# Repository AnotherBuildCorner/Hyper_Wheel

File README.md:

# Multi-Layer Embedded HID Interface with Rotary Input

A programmable HID control interface that replaces discrete key presses with continuous rotary input, enabling precise, context-aware interaction for workflows like video editing and CAD.

**Codename:** Hyper_Wheel

## Engineering Summary

- 4-layer mixed-signal embedded system (98 × 65 mm) based on nRF52840 (BLE + USB HID)
- RF-aware PCB layout with calculated 50Ω antenna trace on TG155 FR4
- Battery-powered architecture (LiPo + charger + protection + load switching)
- Multi-bus I²C system separating OLED displays and encoders for signal integrity
- Designed within JLCPCB DFM constraints (no blind vias, optimized BOM, 0402/0603 preference)
- Staged bring-up strategy using XIAO validation platform to decouple firmware and hardware risk

> > 4-layer mixed-signal PCB with dense MCU fanout, controlled routing, and separated power/RF domains
---

## What This Demonstrates

This project demonstrates the ability to:

- Design a mixed-signal embedded system with RF considerations  
- Make system-level tradeoffs under real constraints (power, layout, manufacturability)  
- Identify and mitigate risk without full simulation tooling  
- Structure hardware bring-up and validation intentionally  

This is not a proof-of-concept—it is a system designed to be built, debugged, and iterated.

---

## Status

- Rev A PCB complete and ready for fabrication  
- Validation hardware in production  
- Firmware development in progress  

---

## Intended Outcome

The goal of this project is to produce a fully functional, portable HID control surface that can be:

- Built using standard PCB manufacturing workflows  
- Assembled and validated without specialized RF tooling  
- Used in real workflows without custom drivers or software dependencies  

Success is defined by reliable operation, predictable behavior, and ease of integration into existing systems.

---

## Concept

### Early Concept Render

> *Early prototype render shown for system concept demonstration. Mechanical design is still evolving.*

Hyper Wheel is a rotary-first HID control surface designed to replace discrete macro inputs with continuous, context-aware control.

The system combines:
- High-resolution rotary encoder input  
- Programmable key matrix  
- Onboard display feedback  

Primary use cases:
- Video editing (timeline scrubbing, precision control)  
- CAD navigation  
- General HID-based workflows  

The design prioritizes:
- Compact form factor  
- Driverless operation (USB/BLE HID only)  
- Integration of continuous and discrete input into a single interface  
---

## System Overview

Hyper Wheel is a programmable HID macro device built around a high-resolution magnetic encoder, designed to provide precise, context-aware control.

Unlike typical macro pads:
- Primary input is continuous (rotary), not discrete  
- Output is standard HID (keyboard + mouse)  
- Feedback is integrated via dual OLED displays  

The system is designed for enterprise compatibility:
- No custom drivers  
- USB and BLE HID only  

Current development focuses on validating:
- Power architecture  
- Multi-layer PCB layout with RF considerations  
- Scalable I/O architecture  

## System Architecture

```mermaid
flowchart LR

%% Power Path
USB[USB 5V] --> CHG[LiPo Charger]
BAT[LiPo Battery] --> PROT[Protection Circuit]
PROT --> CHG
CHG --> SYS[nRF52840 VDDH + Internal Regulator]
PROT --> VMON[ADC Batt Divider]
VMON --> MCU_ADC

%% Core System
SYS --> NRF[nRF52840 MCU] 
SYS --> LS[Load Switches]

%% Peripheral Power
LS --> OLED[Dual OLED Displays]
LS --> ENC[AS5600 Encoders]

%% Data / Control
NRF --> I2C1[I2C Bus 1]
NRF <--> I2C2[I2C Bus 2]
NRF --> LS
I2C1 --> OLED
I2C2 <--> ENC

%% Inputs
KEYS[Keyswitches on GPIO] --> NRF

%% Host Communication
NRF <--> USBDATA[USB 2.0]
NRF --> BLE[BLE]
USBDATA <--> HOST[Host Computer]
BLE --> HOST
```

## Key Features

- nRF52840-based system with **BLE + USB HID support**  
- High-resolution **magnetic encoder (AS5600-based)**  
- Dual **I2C OLED displays** for contextual UI feedback  
- **User-defined key mapping** (firmware-controlled)  
- **Left/right-hand agnostic layout** with mode switching  
- **LiPo + USB power architecture**  
- Modular sensor and expansion strategy  
- Fully **driverless operation (standard HID only)**  

---

## Engineering Highlights

### Single-MCU USB + BLE Architecture
- Transitioned from QFN48 to USB-capable aQFN73 to enable USB HID while maintaining BLE
- Preserved single-MCU architecture to reduce system complexity

### Battery-First Power System
- Implemented Nordic VDDH Config 4 architecture for battery-first operation
- USB used for detection only; system powered from charger output
- Enabled internal DC/DC (DCDCEN0/1), eliminating need for external regulator

### RF Design Approach
- Used reference antenna layout with controlled ground zones
- Calculated 50Ω impedance trace for 2.4 GHz operation on TG155 FR4
- Designed for short-range BLE use (desktop device)
- Validation deferred to hardware bring-up

### Routing Density & Layer Strategy
- Moved key matrix to inner layer to reduce congestion
- Improved fanout of high-density MCU region
- Optimized via sizing for manufacturing cost

### Iteration Strategy (Firmware First)
- Developed XIAO-based validation board to decouple firmware and hardware bring-up
- Allows testing of UI, input pipeline, and HID behavior before full PCB assembly

### Constraint-Driven Design

- Designed without access to RF simulation or SI toolchains, relying on first-principles reasoning and reference layouts to achieve first-pass success  
- Applied calculated trace geometry and conservative design margins to mitigate signal integrity risk  
- Prioritized manufacturability and iteration speed over theoretical optimization  
- Structured design to enable validation through hardware bring-up rather than pre-simulation

---

## Key Engineering Decisions

- **Single-MCU architecture (nRF52840)**  
  Reduced system complexity while supporting both BLE and USB HID

- **Battery-first power design (VDDH Config 4)**  
  Enabled seamless USB + battery operation without conflicting domains

- **Split I²C buses**  
  Prevented address conflicts and improved signal integrity under expansion

- **HID-only communication (no custom drivers)**  
  Ensures enterprise compatibility and plug-and-play behavior

- **Staged bring-up using validation hardware**  
  Reduced risk by separating firmware development from full system assembly

- **Conservative RF design without simulation tooling**  
  Relied on reference layouts and controlled geometry with validation deferred to hardware
---

## Validation Status

| Area | Status |
|------|--------|
| Power System | Not yet characterized under load |
| RF Performance | Not validated (no RF test equipment available) |
| USB Signal Integrity | Not measured |
| I2C Stability | Not stress-tested |
| Firmware Integration | In progress |

> Validation strategy is structured to isolate failure modes early, reducing system-level debugging complexity during full integration

> Firmware bring-up and subsystem testing occurring prior to full hardware integration.

---

## Power Profile (Preliminary)

The following figures are early design estimates based on component datasheets and expected operating modes. Final values will be validated during bring-up.

### Component-Level Current Estimates

| Component / Mode | Estimated Current | Notes |
|------|------:|------|
| nRF52840, BLE active (+8 dBm) | 14.8 mA | Active BLE operating point on 3.3 V rail |
| OLED display (each) | 12–20 mA | 0.96" Winstar OLED at 3.3 V, ~50% illumination |
| AS5600 encoder (each, active) | 6.4 mA | Active measurement mode |
| Keyswitches | ~0 mA | No static consumption |
| nRF52840 system-off, RAM retained, wake on GPIOTE | 2.36 µA | MCU-only low-power state |

### Estimated System Current

| System Mode | Estimated Current | Notes |
|------|------:|------|
| Active, one OLED + one encoder + BLE | ~33.2–41.2 mA | 14.8 + 12–20 + 6.4 |
| Active, two OLEDs + one encoder + BLE | ~45.2–61.2 mA | Current main-board target configuration |
| Active, two OLEDs + two encoders + BLE | ~51.6–67.6 mA | Higher-end fully populated case |
| Deep sleep / system-off | ~33 µA | Includes MCU, charger, protection IC, hall sensor, FET leakage, and battery divider |

### Estimated Runtime (2000 mAh LiPo)

| Mode | Estimated Runtime |
|------|------:|
| 45.2 mA active draw | ~44 hours |
| 61.2 mA active draw | ~33 hours |
| 67.6 mA active draw | ~30 hours |
| 33 µA sleep current | ~6.9 years theoretical |

Sleep-current validation will also include key-matrix wake behavior, since retained GPIO pullups can dominate standby current if not configured carefully.

> Sleep-mode runtime is a first-order electrical estimate only and does not account for battery self-discharge, cell aging, converter losses, or environmental effects.

> These values are estimates and will be validated during hardware bring-up.

##  Hardware Overview

The following images highlight key aspects of the PCB design, including routing strategy, RF layout considerations, and multi-layer power distribution.

---

### Full PCB Layout (Routing View)

> Overall PCB layout showing multi-layer routing strategy, peripheral distribution, and controlled RF region placement.

---

##  MCU / RF Region Detail

### Top Layer (Routing)

> nRF52840 fanout and high-density routing region, including USB interface routing and transition into a controlled antenna region.

---

### Ground Reference Layer

> Ground reference layer showing return path continuity, stitching strategy, and antenna clearance region.

---

### Power Distribution Layer || Metal 4

> Multi-zone power distribution separating 3.3V, Load domains, and ground to reduce coupling and improve system stability.

---

##  Layer Stack & Power Distribution

### Full Ground Plane || Metal 3

> Continuous ground plane providing low-impedance return paths across the board and supporting RF performance.

---

### Full Signal Plane || Metal 2

> Second layer signal plane for BGA fanout.

---

### Full Top Plane || Metal 1

> Primary signal plane with all zone ground.

---

##  Dev Platform / Prototype

> Simplified firmware validation platform based on the XIAO nRF52840, enabling rapid iteration of firmware and UI behavior prior to full hardware validation.

### Dev System Architecture

```mermaid
flowchart LR

%% Power Path
USB[USB 5V] --> CHG[XIAO Onboard LiPo Charger]
BAT[LiPo Battery] --> PROT[Protection Circuit]
PROT --> CHG
CHG --> SYS[XIAO VDDH + Internal Regulator]
PROT --> VMON[ADC Batt Divider]
VMON --> MCU_ADC

%% Core System
SYS --> NRF[nRF52840 MCU] 

%% Peripheral Power
SYS --> OLED[Dual OLED Displays]
SYS --> ENC[AS5600 Encoders]

%% Data / Control
NRF <--> I2C1[I2C Bus 1]
I2C1 <--> OLED
I2C1 <--> ENC

%% Inputs
KEYS[Keyswitches on GPIO] --> NRF

%% Host Communication
NRF <--> USBDATA[USB 2.0]
NRF --> BLE[BLE]
USBDATA <--> HOST[Host Computer]
BLE --> HOST
```

---

## Hardware Iterations

### Rev A – Firmware Validation Platform
- XIAO nRF52840-based
- Reduced feature set to validate input, display, and HID stack
- 2-layer board for reduced cost/complexity

.png>) 
> Rev A Board.

.png>)
> Rev B board, note change in keyswitch footprints and added jumper network
### Rev B – Connector + Layout Refinement
- Introduced JST right-angle connectors (2/4/6 pin)
- Retained 2.54mm headers for bring-up flexibility
- Implemented rotationally symmetric connector layout
  - Enables cross-compatibility between 4-pin and 6-pin harnesses
  - Increased routing complexity but improved wiring consistency
- Adjusted OLED power routing for improved modularity

.png>).png>)
> Right shows the reconfigurable jumper array to switch GND and VCC pins to OLED

### Key Takeaways
- Connector standardization impacts both layout complexity and user error rate
- Bring-up flexibility is worth temporary redundancy (2.54 + JST)
- Physical interface decisions cascade into firmware, assembly, and usability

## Design for Manufacturing (DFM)

This design explicitly considers **PCBA cost and manufacturability**, not just functionality.

- Designed within standard JLCPCB capabilities (no blind vias, no via-in-pad)  
- Optimized via sizing for cost  
- Minimized use of 0201 components where not required  
- Favoring 0402 / 0603 for improved assembly yield  
- Reducing unique BOM values (ongoing)

This ensures the design is **practical for real-world assembly**, not just theoretical performance.

---

##  Assembly / 3D Model

.png>)
> Not all components have linked 3D models. USB and Keyswitches not shown
---

## Current Status

### Hardware
- Main PCB: Ready for fabrication (Rev A)  
- XIAO-based validation boards: Fabricated, awaiting delivery  
- Power architecture implemented (VDDH-based system)  
- Multi-layer routing and RF region defined  
- Test points and debug access integrated  

### Firmware
- Early development in progress (PlatformIO)  
- HID architecture defined (USB + BLE)  
- Encoder and display integration in progress  
- UI/UX layer not yet implemented  

### Mechanical
- Concept prototype complete (wheel + macro pad)  
- Final enclosure design pending  
- Mounting and integration strategy in development  

---

### Next Milestones

1. Bring-up XIAO validation platform  
2. Validate encoder and OLED pipeline  
3. Verify power behavior under real load  
4. Assemble Rev A main board  
5. Begin enclosure integration  

---

## Design Constraints

- Designed for standard PCB manufacturing (JLCPCB) with no blind/buried vias  
- Limited board size due to encoder geometry and enclosure constraints  
- Required HID-only communication for enterprise compatibility  
- Power system designed around single-cell LiPo with safe charge/discharge behavior

### Key Tradeoffs

- Chose single-MCU (nRF52840) over multi-chip architecture to reduce system complexity at the cost of tighter routing constraints  
- Accepted lack of RF simulation tooling and relied on reference layout + conservative design margins  
- Used internal VDDH regulation to simplify power architecture, trading off external regulator flexibility  
- Split I2C buses to manage address conflicts and maintain signal integrity under expansion

---
## Use Cases

**Primary**
- Video editing (timeline scrubbing, precision control)

**Secondary**
- CAD navigation  
- General productivity workflows  
- Custom macro environments  

---

## Future Work

### Firmware

- Development of configurable HID mapping system  
- Exploration of QMK/ZMK compatibility with encoder-based input  
- Potential on-device configuration interface via OLED UI  

### Mechanical

- Final enclosure design around encoder and key layout  
- Mounting strategy for PCB and battery integration  
- Ergonomic considerations for left/right-handed use

---

## Design Philosophy

- Use **standard HID** instead of custom drivers  
- Prioritize **iteration speed over theoretical perfection**  
- Design within **real manufacturing constraints**  
- Document decisions and tradeoffs explicitly

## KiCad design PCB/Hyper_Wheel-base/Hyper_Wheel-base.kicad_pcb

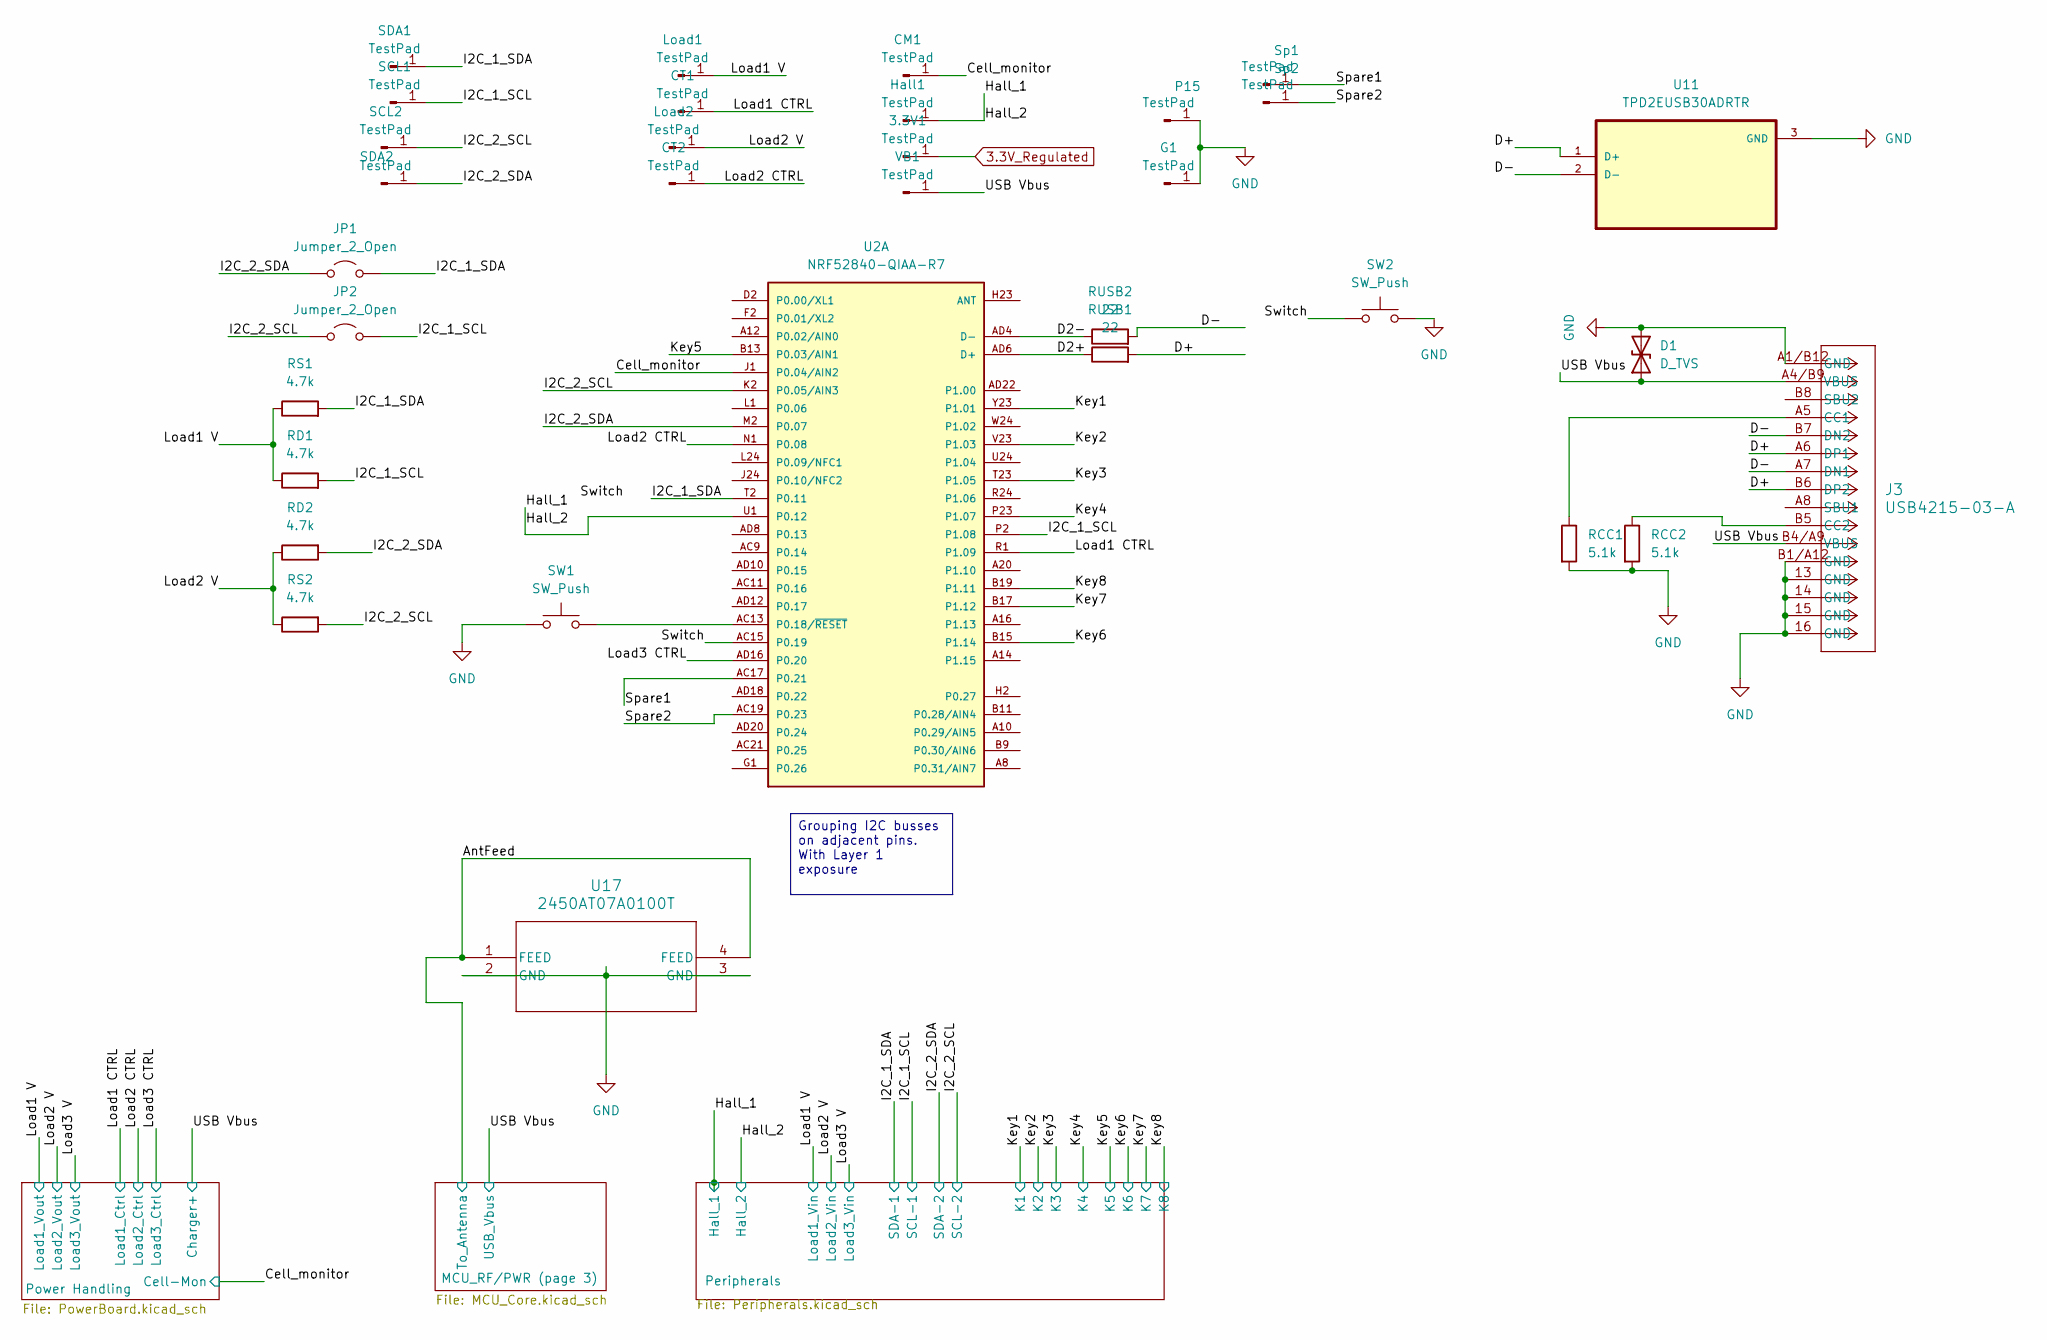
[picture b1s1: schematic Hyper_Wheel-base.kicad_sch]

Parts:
3.3V1: TestPad; TestPoint_Pad_D1.0mm
CM1: TestPad; TestPoint_Pad_D1.0mm
CT1, CT2: TestPad; TestPoint_Pad_D1.0mm
D1: D_TVS; D_0603_1608Metric
G1: TestPad; TestPoint_Pad_D1.0mm
Hall1: TestPad; TestPoint_Pad_D1.0mm
J3: USB4215-03-A; USBC-CONN_8p94X6p5X3p16_12L_GCC
JP1, JP2: Jumper_2_Open; SolderJumper-2_P1.3mm_Open_Pad1.0x1.5mm
Load1, Load2: TestPad; TestPoint_Pad_D1.0mm
P15: TestPad; TestPoint_Pad_D1.0mm
RCC1, RCC2: 5.1k; R_0402_1005Metric
RD1, RD2: 4.7k; R_0402_1005Metric
RS1, RS2: 4.7k; R_0402_1005Metric
RUSB1, RUSB2: 22; R_0402_1005Metric
SCL1, SCL2: TestPad; TestPoint_Pad_D1.0mm
SDA1, SDA2: TestPad; TestPoint_Pad_D1.0mm
SW1, SW2: SW_Push; SW_SPST_PTS647_Sx38
Sp1, Sp2: TestPad; TestPoint_Pad_D1.0mm
U2: NRF52840-QIAA-R7; NORDIC_NRF52840-QIAA-R7; PARTREV 1.2
U11: TPD2EUSB30ADRTR; SOT-323_SC-70
U17: 2450AT07A0100T; 2450AT07A0100T_JOT+Keepout
VB1: TestPad; TestPoint_Pad_D1.0mm

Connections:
3.3V_Regulated: 3.3V1.1 (Pin_1_1); also elsewhere on the board
/AntFeed: U17.1 (FEED), U17.4 (FEED); also elsewhere on the board
/Cell_monitor: CM1.1 (Pin_1_1), U2.J1 (P0.04/AIN2); also elsewhere on the board
/D2+: RUSB1.1, U2.AD6 (D+)
/D2-: RUSB2.1, U2.AD4 (D-)
/D+: J3.A6 (DP1), J3.B6 (DP2), RUSB1.2, U11.1 (D+)
/D-: J3.A7 (DN1), J3.B7 (DN2), RUSB2.2, U11.2 (D-)
/Hall_1: Hall1.1 (Pin_1_1), U2.U1 (P0.12); also elsewhere on the board
/I2C_1_SCL: JP2.2 (B), RD1.2, SCL1.1 (Pin_1_1), U2.P2 (P1.08); also elsewhere on the board
/I2C_1_SDA: JP1.2 (B), RS1.2, SDA1.1 (Pin_1_1), U2.T2 (P0.11); also elsewhere on the board
/I2C_2_SCL: JP2.1 (A), RS2.2, SCL2.1 (Pin_1_1), U2.K2 (P0.05/AIN3); also elsewhere on the board
/I2C_2_SDA: JP1.1 (A), RD2.2, SDA2.1 (Pin_1_1), U2.M2 (P0.07); also elsewhere on the board
/Key1: U2.Y23 (P1.01); also elsewhere on the board
/Key2: U2.V23 (P1.03); also elsewhere on the board
/Key3: U2.T23 (P1.05); also elsewhere on the board
/Key4: U2.P23 (P1.07); also elsewhere on the board
/Key5: U2.B13 (P0.03/AIN1); also elsewhere on the board
/Key6: U2.B15 (P1.14); also elsewhere on the board
/Key7: U2.B17 (P1.12); also elsewhere on the board
/Key8: U2.B19 (P1.11); also elsewhere on the board
/Load1 CTRL: CT1.1 (Pin_1_1), U2.R1 (P1.09); also elsewhere on the board
/Load1 V: Load1.1 (Pin_1_1), RD1.1, RS1.1; also elsewhere on the board
/Load2 CTRL: CT2.1 (Pin_1_1), U2.N1 (P0.08); also elsewhere on the board
/Load2 V: Load2.1 (Pin_1_1), RD2.1, RS2.1; also elsewhere on the board
/Load3 CTRL: U2.AD16 (P0.20)
/Spare1: Sp1.1 (Pin_1_1), U2.AC17 (P0.21)
/Spare2: Sp2.1 (Pin_1_1), U2.AC19 (P0.23)
/Switch: SW2.1, U2.AC15 (P0.19)
/USB Vbus: D1.1 (A1), J3.A4/B9 (VBUS), J3.B4/A9 (VBUS), VB1.1 (Pin_1_1); also elsewhere on the board
GND: D1.2 (A2), G1.1 (Pin_1_1), J3.13 (GND), J3.14 (GND), J3.15 (GND), J3.16 (GND), J3.A1/B12 (GND), J3.B1/A12 (GND), P15.1 (Pin_1_1), RCC1.2, RCC2.2, SW1.1, SW2.2, U11.3 (GND), U17.2 (GND), U17.3 (GND); also elsewhere on the board
unnamed: J3.A5 (CC1), RCC1.1
unnamed: J3.B5 (CC2), RCC2.1
unnamed: SW1.2, U2.AC13 (P0.18/~RESET)
unnamed 57: U2.H23 (ANT); also elsewhere on the board
unnamed 65: U2.D2 (P0.00/XL1); also elsewhere on the board
unnamed 66: U2.F2 (P0.01/XL2); also elsewhere on the board

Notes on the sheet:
Grouping I2C busses on adjacent pins. With Layer 1 exposure

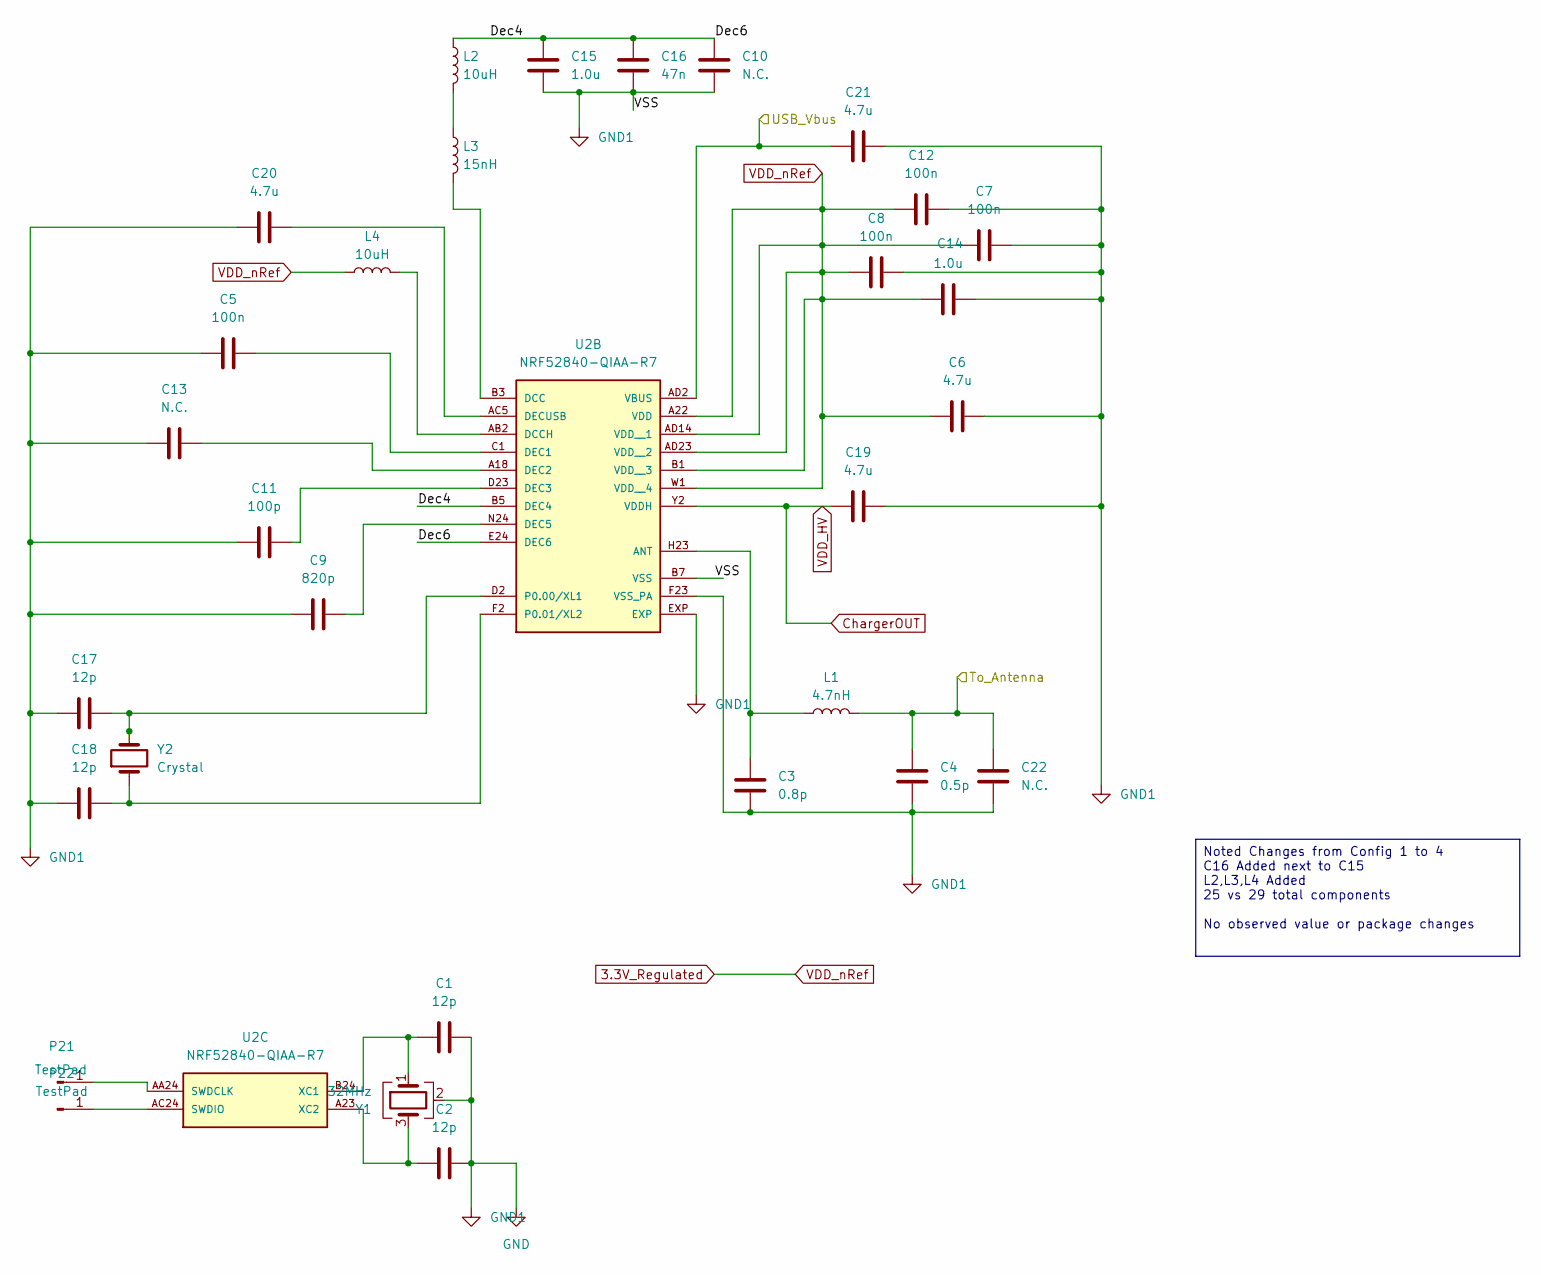
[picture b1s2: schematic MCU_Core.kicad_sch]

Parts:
C1, C2, C17, C18: 12p; C_0402_1005Metric
C3: 0.8p; C_0402_1005Metric
C4: 0.5p; C_0402_1005Metric
C5, C7, C8, C12: 100n; C_0402_1005Metric
C6, C19, C20, C21: 4.7u; C_0603_1608Metric
C9: 820p; C_0402_1005Metric
C10, C13, C22: N.C.; C_0402_1005Metric
C11: 100p; C_0402_1005Metric
C14, C15: 1.0u; C_0603_1608Metric
C16: 47n; C_0402_1005Metric
L1: 4.7nH; L_0402_1005Metric
L2, L4: 10uH; L_0603_1608Metric
L3: 15nH; L_0402_1005Metric
P21, P22: TestPad; TestPoint_Pad_D1.0mm
U2: NRF52840-QIAA-R7; NORDIC_NRF52840-QIAA-R7; PARTREV 1.2
Y1: 32MHz; Crystal_SMD_2016-4Pin_2.0x1.6mm
Y2: Crystal

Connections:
3.3V_Regulated: C6.1, C7.1, C8.1, C12.1, C14.1, L4.1, U2.A22 (VDD), U2.AD14 (VDD__1), U2.AD23 (VDD__2), U2.B1 (VDD__3), U2.W1 (VDD__4); also elsewhere on the board
/AntFeed: C4.2, C22.1, L1.2; also elsewhere on the board
/MCU_RF/PWR (page 3)/Dec4: C10.2, C15.2, C16.2, L2.1, U2.B5 (DEC4), U2.E24 (DEC6)
/USB Vbus: C21.1, U2.AD2 (VBUS); also elsewhere on the board
ChargerOUT: C19.1, U2.Y2 (VDDH); also elsewhere on the board
GND: C1.2, C2.2, C3.1, C4.1, C5.1, C6.2, C7.2, C8.2, C9.1, C10.1, C11.1, C12.2, C13.1, C14.2, C15.1, C16.1, C17.1, C18.1, C19.2, C20.1, C21.2, C22.2, U2.B7 (VSS), U2.EXP, U2.F23 (VSS_PA), Y1.2 (G), Y1.4 (G); also elsewhere on the board
unnamed: L2.2, L3.1
unnamed: P21.1 (Pin_1_1), U2.AA24 (SWDCLK)
unnamed: P22.1 (Pin_1_1), U2.AC24 (SWDIO)
unnamed: C3.2, L1.1, U2.H23 (ANT)
unnamed: L3.2, U2.B3 (DCC)
unnamed: L4.2, U2.AB2 (DCCH)
unnamed: C5.2, U2.C1 (DEC1)
unnamed: C13.2, U2.A18 (DEC2)
unnamed: C11.2, U2.D23 (DEC3)
unnamed: C9.2, U2.N24 (DEC5)
unnamed: C20.2, U2.AC5 (DECUSB)
unnamed: C17.2, U2.D2 (P0.00/XL1), Y2.2
unnamed: C18.2, U2.F2 (P0.01/XL2), Y2.1
unnamed: C1.1, U2.B24 (XC1), Y1.1
unnamed: C2.1, U2.A23 (XC2), Y1.3

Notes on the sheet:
Noted Changes from Config 1 to 4 C16 Added next to C15 L2,L3,L4 Added 25 vs 29 total components No observed value or package changes

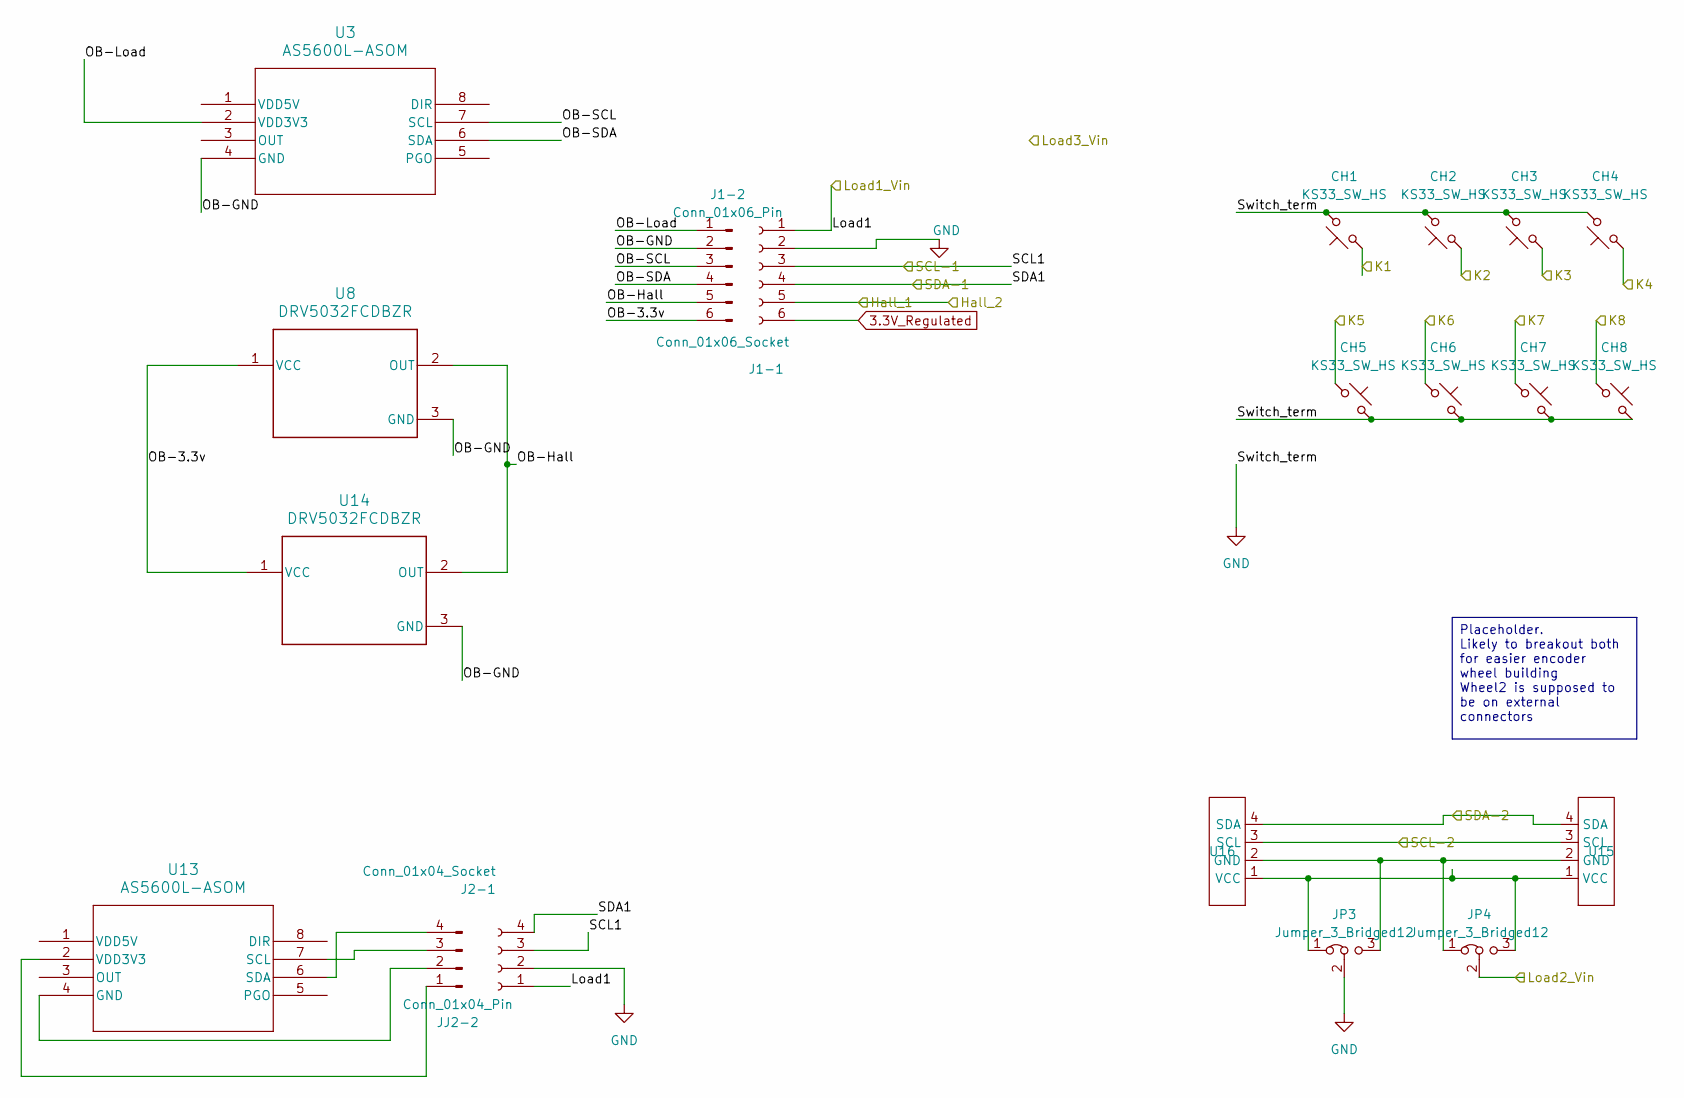
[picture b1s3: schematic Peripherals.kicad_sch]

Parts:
CH1, CH2, CH3, CH4, CH5, CH6, CH7, CH8: KS33_SW_HS; SW_KS33_HS_KS-2P02B01-02_HS_1u
J1-1: Conn_01x06_Socket; PinHeader_1x06_P2.54mm_Vertical
J1-2: Conn_01x06_Pin
J2-1: Conn_01x04_Socket; PinHeader_1x04_P2.54mm_Vertical
JJ2-2: Conn_01x04_Pin
JP3, JP4: Jumper_3_Bridged12; SolderJumper-3_P1.3mm_Bridged12_Pad1.0x1.5mm
U3, U13: AS5600L-ASOM; AS5600L-ASOM_AMS
U8, U14: DRV5032FCDBZR; DRV5032-DBZ0003A-IPC_A
U15, U16: OLED 128x64

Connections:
3.3V_Regulated: J1-1.6; also elsewhere on the board
/Hall_1: J1-1.5; also elsewhere on the board
/I2C_1_SCL: J1-1.3, J2-1.3; also elsewhere on the board
/I2C_1_SDA: J1-1.4, J2-1.4; also elsewhere on the board
/I2C_2_SCL: U15.3 (SCL), U16.3 (SCL); also elsewhere on the board
/I2C_2_SDA: U15.4 (SDA), U16.4 (SDA); also elsewhere on the board
/Key1: CH1.1; also elsewhere on the board
/Key2: CH2.1; also elsewhere on the board
/Key3: CH3.1; also elsewhere on the board
/Key4: CH4.1; also elsewhere on the board
/Key5: CH5.1; also elsewhere on the board
/Key6: CH6.1; also elsewhere on the board
/Key7: CH7.1; also elsewhere on the board
/Key8: CH8.1; also elsewhere on the board
/Load1 V: J1-1.1, J2-1.1; also elsewhere on the board
/Load2 V: JP4.2 (C); also elsewhere on the board
/Peripherals/OB-3.3v: J1-2.6, U8.1 (VCC), U14.1 (VCC)
/Peripherals/OB-GND: J1-2.2, U3.4 (GND), U8.3 (GND), U14.3 (GND)
/Peripherals/OB-Hall: J1-2.5, U8.2 (OUT), U14.2 (OUT)
/Peripherals/OB-Load: J1-2.1, U3.2 (VDD3V3)
/Peripherals/OB-SCL: J1-2.3, U3.7 (SCL)
/Peripherals/OB-SDA: J1-2.4, U3.6 (SDA)
GND: CH1.2, CH2.2, CH3.2, CH4.2, CH5.2, CH6.2, CH7.2, CH8.2, J1-1.2, J2-1.2, JP3.2 (C); also elsewhere on the board
unnamed: JJ2-2.1, U13.2 (VDD3V3)
unnamed: JJ2-2.2, U13.4 (GND)
unnamed: JJ2-2.3, U13.7 (SCL)
unnamed: JJ2-2.4, U13.6 (SDA)
unnamed: JP3.1 (A), JP4.3 (B), U15.1 (GND), U16.1 (GND)
unnamed: JP3.3 (B), JP4.1 (A), U15.2 (VCC), U16.2 (VCC)

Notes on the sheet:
Placeholder. Likely to breakout both for easier encoder wheel building Wheel2 is supposed to be on external connectors

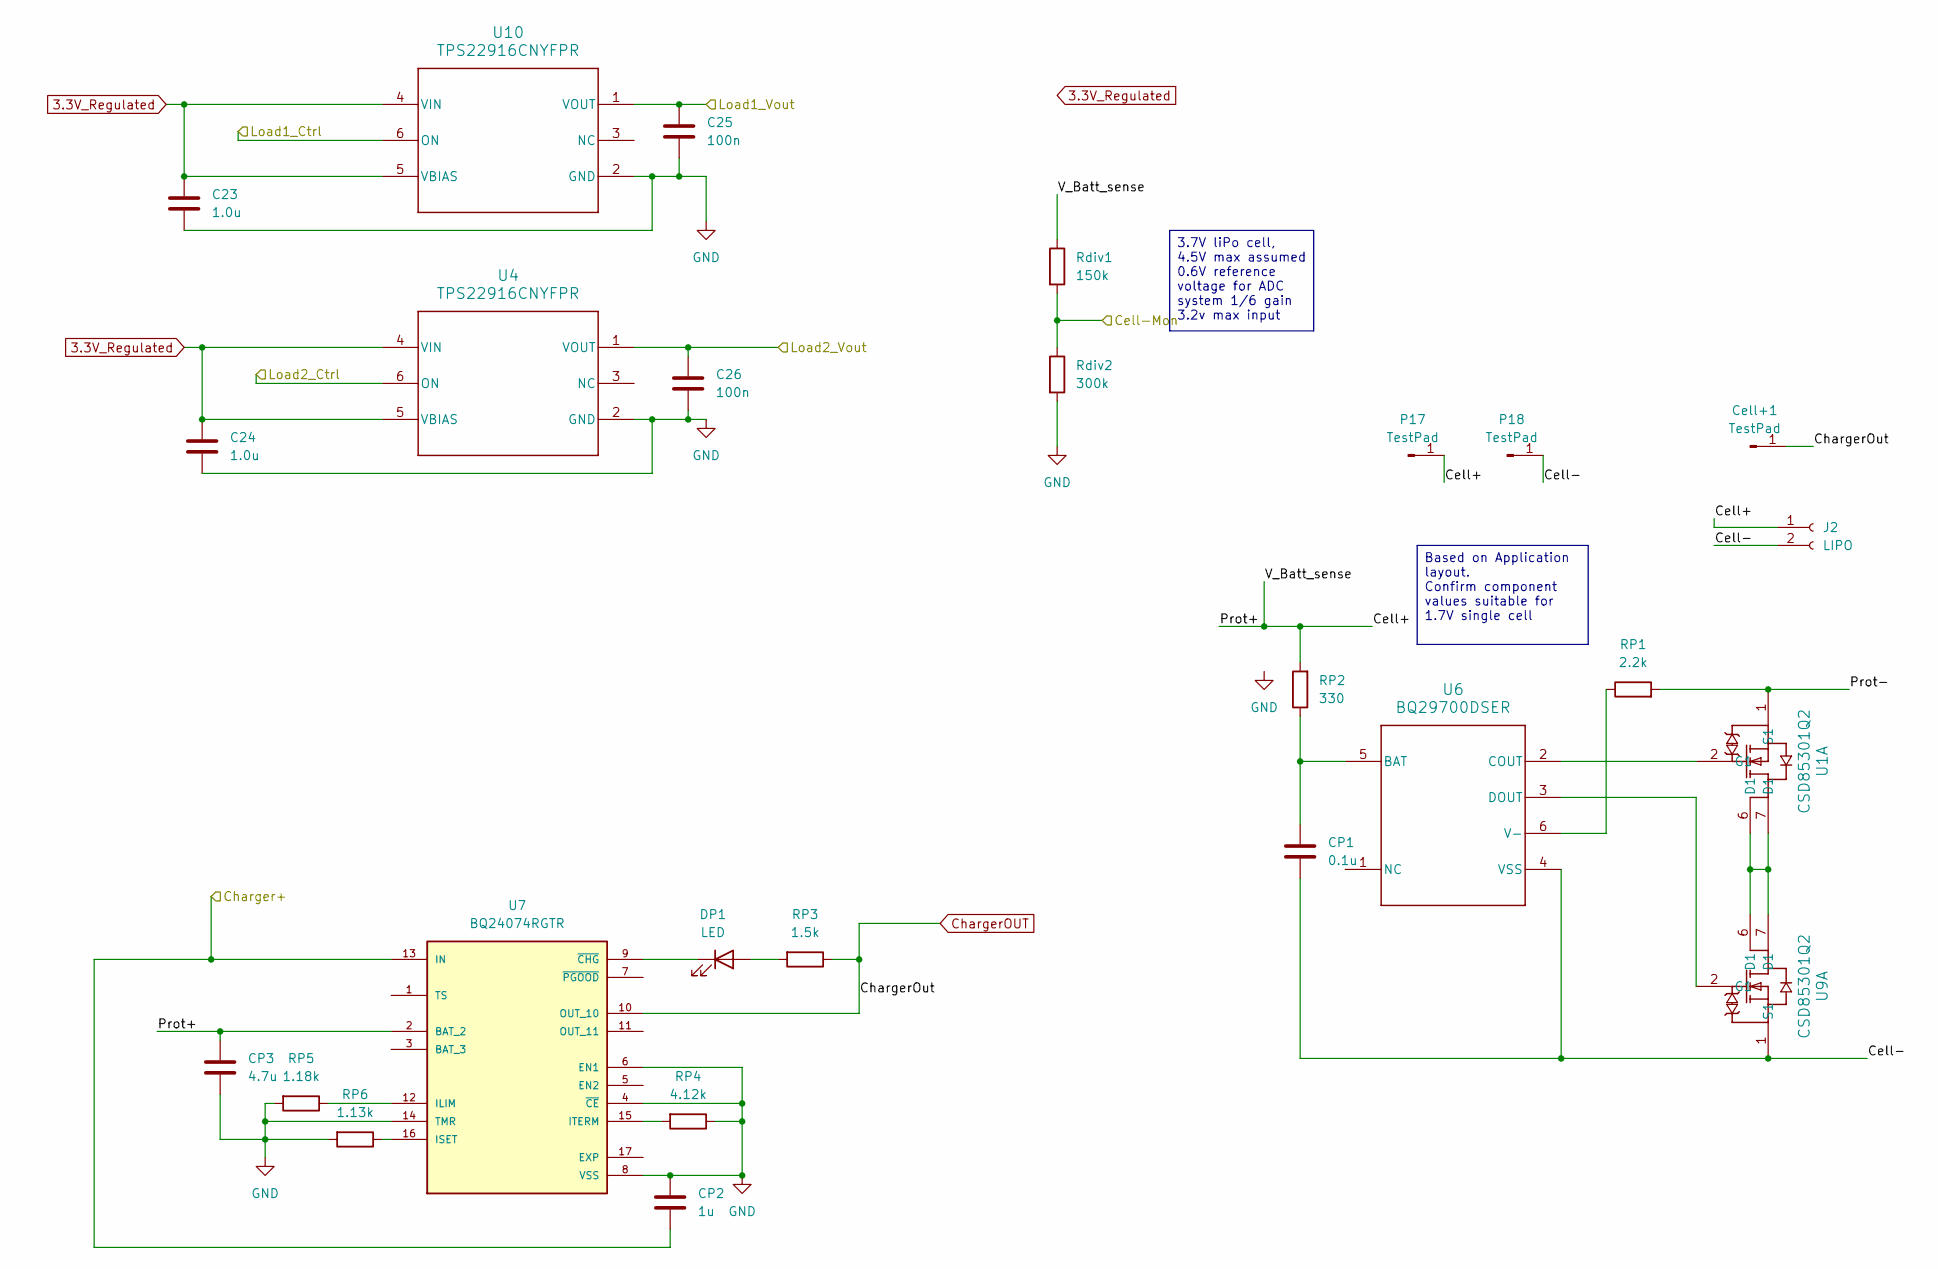
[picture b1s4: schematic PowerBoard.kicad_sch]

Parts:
C23, C24: 1.0u; C_0603_1608Metric
C25, C26: 100n; C_0402_1005Metric
CP1: 0.1u; C_0201_0603Metric_Pad0.64x0.40mm_HandSolder
CP2: 1u; C_0201_0603Metric_Pad0.64x0.40mm_HandSolder
CP3: 4.7u; C_0201_0603Metric_Pad0.64x0.40mm_HandSolder
Cell+1: TestPad; TestPoint_Pad_D1.0mm
DP1: LED; LED_0603_1608Metric
J2: LIPO; JST_EH_B2B-EH-A_1x02_P2.50mm_Vertical
P17, P18: TestPad; TestPoint_Pad_D1.0mm
RP1: 2.2k; R_0603_1608Metric_Pad0.98x0.95mm_HandSolder
RP2: 330; R_0603_1608Metric_Pad0.98x0.95mm_HandSolder
RP3: 1.5k; R_0603_1608Metric_Pad0.98x0.95mm_HandSolder
RP4: 4.12k; R_0603_1608Metric_Pad0.98x0.95mm_HandSolder
RP5: 1.18k; R_0603_1608Metric_Pad0.98x0.95mm_HandSolder
RP6: 1.13k; R_0603_1608Metric_Pad0.98x0.95mm_HandSolder
Rdiv1: 150k; R_0603_1608Metric
Rdiv2: 300k; R_0603_1608Metric
U1, U9: CSD85301Q2; CDS85301-DQK0006B
U4, U10: TPS22916CNYFPR; DBV0006A_L
U6: BQ29700DSER; BQ29700-DSE0006A
U7: BQ24074RGTR; BQ24074-QFN50P300X300X100-17N; PARTREV M

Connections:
3.3V_Regulated: C23.2, C24.2, U4.4 (VIN), U4.5 (VBIAS), U10.4 (VIN), U10.5 (VBIAS); also elsewhere on the board
/Cell_monitor: Rdiv1.2, Rdiv2.1; also elsewhere on the board
/Load1 CTRL: U10.6 (ON); also elsewhere on the board
/Load1 V: C25.2, U10.1 (VOUT); also elsewhere on the board
/Load2 CTRL: U4.6 (ON); also elsewhere on the board
/Load2 V: C26.2, U4.1 (VOUT); also elsewhere on the board
/Power Handling/Cell+: CP3.1, J2.1, P17.1 (Pin_1_1), RP2.2, Rdiv1.1, U7.2 (BAT_2)
/Power Handling/Cell-: CP1.2, J2.2, P18.1 (Pin_1_1), U6.4 (VSS), U9.1 (S1)
/Power Handling/Prot-: RP1.2, U1.1 (S1)
/USB Vbus: CP2.2, U7.13 (IN); also elsewhere on the board
ChargerOUT: Cell+1.1 (Pin_1_1), RP3.1, U7.10 (OUT_10); also elsewhere on the board
GND: C23.1, C24.1, C25.1, C26.1, CP2.1, CP3.2, RP4.1, RP5.2, RP6.2, Rdiv2.2, U4.2 (GND), U7.4 (~CE), U7.6 (EN1), U7.8 (VSS), U7.14 (TMR), U10.2 (GND); also elsewhere on the board
unnamed: DP1.2 (A), RP3.2
unnamed: DP1.1 (K), U7.9 (~CHG)
unnamed: U1.6 (D1), U1.7 (D1), U9.6 (D1), U9.7 (D1)
unnamed: U1.2 (G1), U6.2 (COUT)
unnamed: CP1.1, RP2.1, U6.5 (BAT)
unnamed: U6.3 (DOUT), U9.2 (G1)
unnamed: RP1.1, U6.6 (V-)
unnamed: RP5.1, U7.12 (ILIM)
unnamed: RP6.1, U7.16 (ISET)
unnamed: RP4.2, U7.15 (ITERM)

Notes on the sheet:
3.7V liPo cell, 4.5V max assumed 0.6V reference voltage for ADC system 1/6 gain 3.2v max input
Based on Application layout. Confirm component values suitable for 1.7V single cell

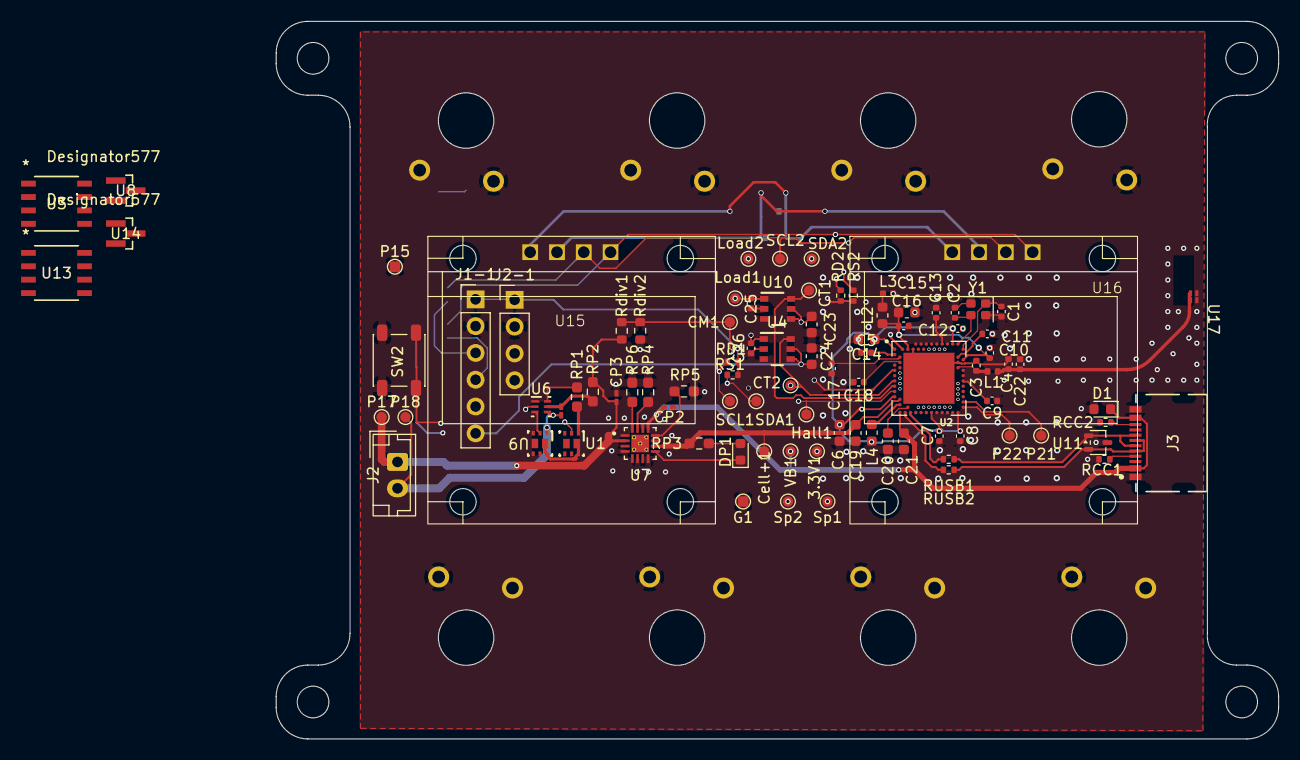
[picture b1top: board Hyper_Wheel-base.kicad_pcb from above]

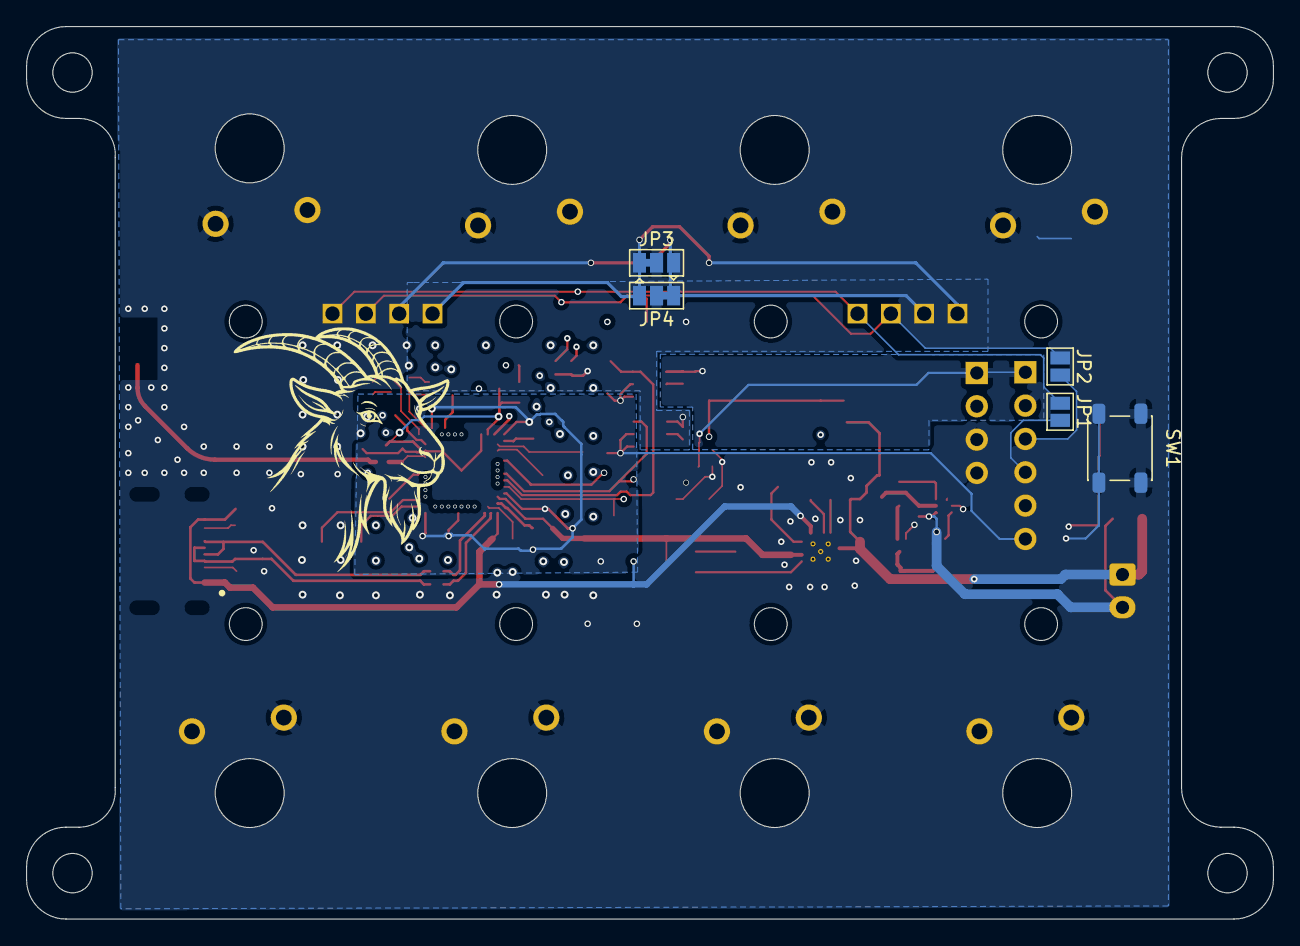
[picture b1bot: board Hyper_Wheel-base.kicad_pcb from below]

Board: 4 copper layers, 95.0 x 68.0 mm, 106 parts (5 on the bottom side), 67 nets.

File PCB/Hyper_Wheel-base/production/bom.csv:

Designator,Footprint,Quantity,Value,LCSC Part #
"C1, C17, C18, C2",0402,4,12p,
"C10, C13, C22",0402,3,N.C.,
C11,0402,1,100p,
"C12, C25, C26, C5, C7, C8",0402,6,100n,
"C14, C15, C23, C24",0603,4,1.0u,
C16,0402,1,47n,
"C19, C20, C21, C6",0603,4,4.7u,
C3,0402,1,0.8p,
C4,0402,1,0.5p,
C9,0402,1,820p,
"CH1, CH2, CH3, CH4, CH5, CH6, CH7, CH8",SW_KS33_HS_KS-2P02B01-02_HS_1u,8,KS33_SW_HS,
CP1,0201,1,0.1u,
CP2,0201,1,1u,
CP3,0201,1,4.7u,
D1,0603,1,D_TVS,
DP1,0603,1,LED,
J1-1,PinHeader_1x06_P2.54mm_Vertical,1,Conn_01x06_Socket,
J2,JST_EH_B2B-EH-A_1x02_P2.50mm_Vertical,1,LIPO,
J2-1,PinHeader_1x04_P2.54mm_Vertical,1,Conn_01x04_Socket,
J3,USBC-CONN_8p94X6p5X3p16_12L_GCC,1,USB4215-03-A,
"JP1, JP2",SolderJumper-2_P1.3mm_Open_Pad1.0x1.5mm,2,Jumper_2_Open,
L1,0402,1,4.7nH,
"L2, L4",0603,2,10uH,
L3,0402,1,15nH,
"RCC1, RCC2",0402,2,5.1k,
"RD1, RD2, RS1, RS2",0402,4,4.7k,
RDIV1,0603,1,150k,
RDIV2,0603,1,300k,
RP1,0603,1,2.2k,
RP2,0603,1,330,
RP3,0603,1,1.5k,
RP4,0603,1,4.12k,
RP5,0603,1,1.18k,
RP6,0603,1,1.13k,
"RUSB1, RUSB2",0402,2,22,
"SW1, SW2",SW_SPST_PTS647_Sx38,2,SW_Push,
"U1, U9",CDS85301-DQK0006B,2,CSD85301Q2,
"U10, U4",DBV0006A_L,2,TPS22916CNYFPR,
U11,SOT-323_SC-70,1,TPD2EUSB30ADRTR,
"U13, U3",AS5600L-ASOM_AMS,2,AS5600L-ASOM,
"U14, U8",DRV5032-DBZ0003A-IPC_A,2,DRV5032FCDBZR,
"U15, U16",OLED 128x64,2,~,
U17,2450AT07A0100T_JOT+Keepout,1,2450AT07A0100T,
U2,NORDIC_NRF52840-QIAA-R7,1,NRF52840-QIAA-R7,
U6,BQ29700-DSE0006A,1,BQ29700DSER,
U7,BQ24074-QFN50P300X300X100-17N,1,BQ24074RGTR,
Y1,Crystal_SMD_2016-4Pin_2.0x1.6mm,1,32MHz,
